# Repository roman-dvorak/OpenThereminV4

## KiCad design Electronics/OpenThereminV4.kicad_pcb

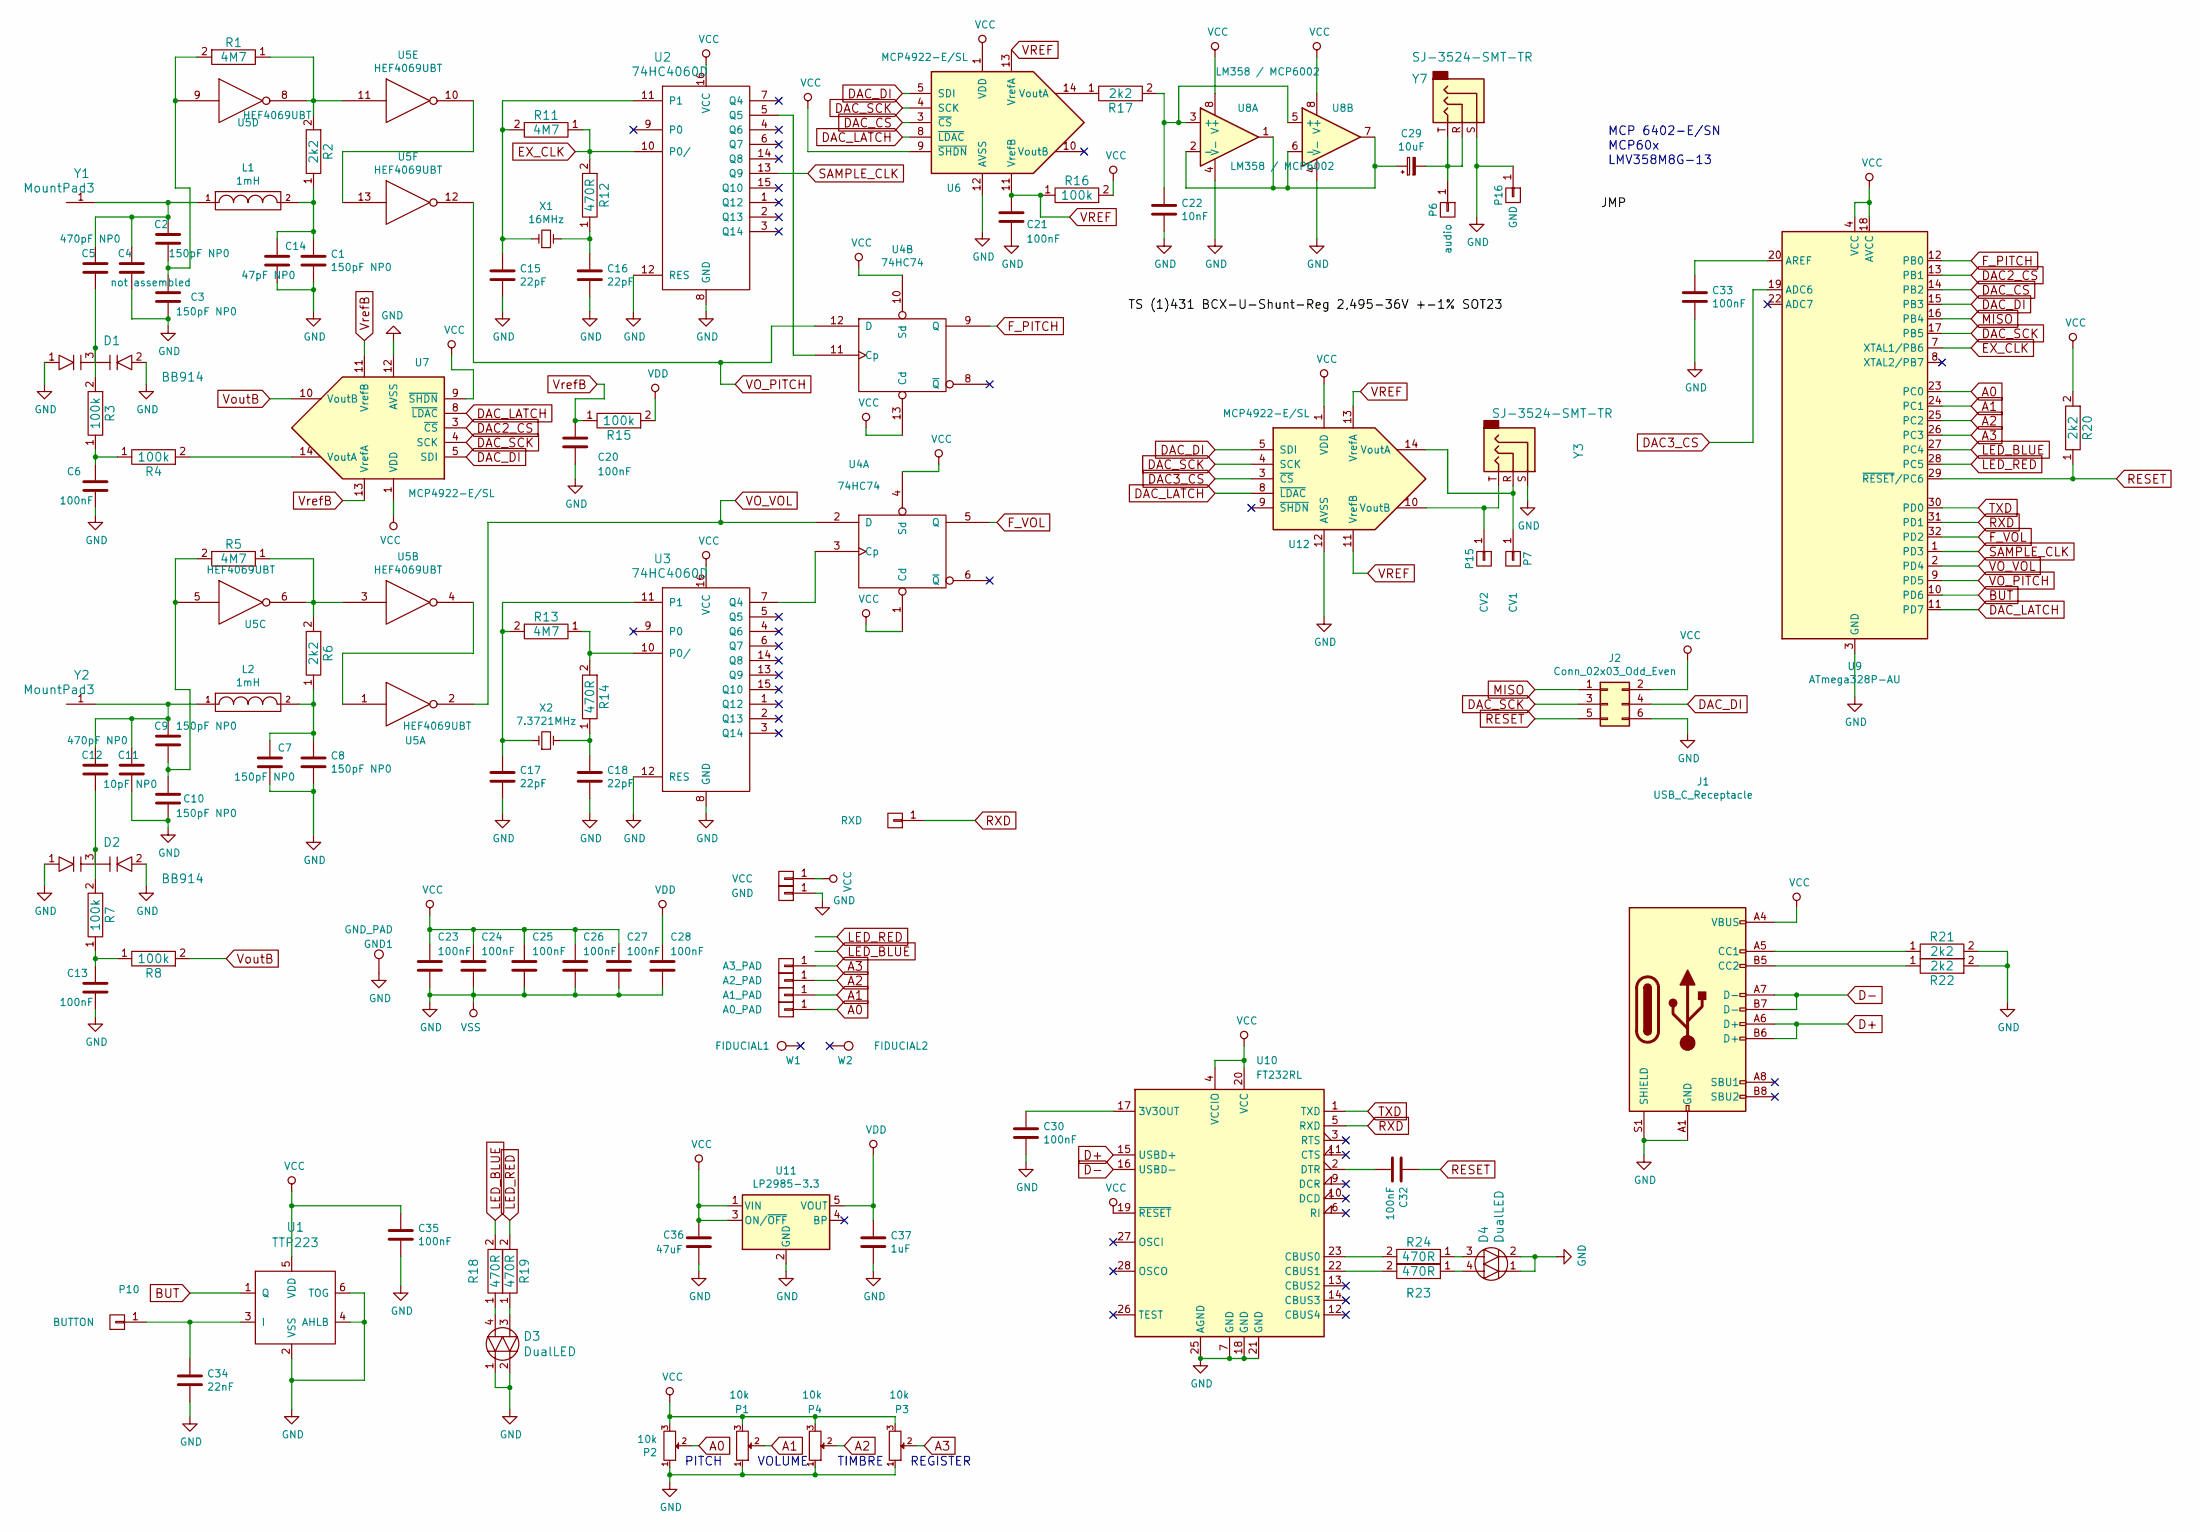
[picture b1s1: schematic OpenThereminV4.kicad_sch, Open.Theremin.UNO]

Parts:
C1, C2, C3, C7, C8, C9, C10: 150pF NP0; C_0603_1608Metric; mouser OK NPO
C4: not assembled; C_0603_1608Metric
C5, C12: 470pF NP0; C_0603_1608Metric; mouser OK NPO
C6, C13, C20, C21, C23, C24, C25, C26, C27, C28, C30, C32, C33, C35: 100nF; C_0603_1608Metric; mouser OK
C11: 10pF NP0; C_0603_1608Metric; mouser OK NPO
C14: 47pF NP0; C_0603_1608Metric; mouser OK NPO
C15, C16, C17, C18: 22pF; C_0603_1608Metric; mouser OK
C22: 10nF; C_0603_1608Metric; mouser OK
C29: 10uF; C_0805_2012Metric; mouser OK
C34: 22nF; C_0603_1608Metric; mouser OK
C36: 47uF; C_1206_3216Metric; mouser OK
C37: 1uF; C_0603_1608Metric; mouser OK
D1, D2: BB914; SOT-23; mouser OK
D3, D4: DualLED; LED_DUAL_WL-SBRW; mouser OK
GND1: GND_PAD; MountingHole_3mm_Pad_Via
J1: USB_C_Receptacle; USBC GCT_USB4105-GF-A; mouser OK
J2: Conn_02x03_Odd_Even; Tag-Connect_TC2030-IDC-NL_2x03_P1.27mm_Vertical
L1, L2: 1mH; L_1812_4532Metric; mouser OK
P1, P2, P3, P4: 10k; PS15NV60; mouser OK
P5: RXD; TestPoint_Pad_1.5x1.5mm
P6: audio; TestPoint_Pad_1.5x1.5mm
P7: CV1; TestPoint_Pad_1.5x1.5mm
P8: VCC; TestPoint_Pad_1.5x1.5mm
P9, P16: GND; TestPoint_Pad_1.5x1.5mm
P10: BUTTON; SensorButton
P11: A3_PAD; TestPoint_Pad_1.5x1.5mm
P12: A2_PAD; TestPoint_Pad_1.5x1.5mm
P13: A1_PAD; TestPoint_Pad_1.5x1.5mm
P14: A0_PAD; TestPoint_Pad_1.5x1.5mm
P15: CV2; TestPoint_Pad_1.5x1.5mm
R1, R5, R11, R13: 4M7; R_0603_1608Metric; mouser OK
R2, R6, R17, R20, R21, R22: 2k2; R_0603_1608Metric; mouser OK
R3, R4, R7, R8, R15, R16: 100k; R_0603_1608Metric; mouser OK
R12, R14, R18, R19, R23, R24: 470R; R_0603_1608Metric; mouser OK
U1: TTP223; SOT-23-6; mouser dratek/dis
U2, U3: 74HC4060D; SOIC-16_3.9x9.9mm_P1.27mm; mouser OK
U4: 74HC74; SOIC-14_3.9x8.7mm_P1.27mm; mouser OK
U5: HEF4069UBT; SOIC-14_3.9x8.7mm_P1.27mm; mouser OK
U6, U7, U12: MCP4922-E/SL; SOIC-14_3.9x8.7mm_P1.27mm; mouser LCSC
U8: LM358 / MCP6002; SOIC-8_3.9x4.9mm_P1.27mm; mouser OK
U9: ATmega328P-AU; TQFP-32_7x7mm_P0.8mm; mouser LCSC
U10: FT232RL; SSOP-28_5.3x10.2mm_P0.65mm; mouser LCSC
U11: LP2985-3.3; SOT-23-5; mouser OK
W1: FIDUCIAL1; Fiducial_1mm_Mask2mm
W2: FIDUCIAL2; Fiducial_1mm_Mask2mm
X1: 16MHz; Crystal_SMD_HC49-SD; mouser OK
X2: 7.3721MHz; Crystal_SMD_HC49-SD; mouser Ok
Y1, Y2: MountPad3; AntennaMountHole; mouser OK
Y3, Y7: SJ-3524-SMT-TR; Jack_3.5mm_CUI_SJ-3524-SMT_Horizontal; mouser OK

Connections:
A0: P2.2, P14.1, U9.23 (PC0)
A1: P1.2, P13.1, U9.24 (PC1)
A2: P4.2, P12.1, U9.25 (PC2)
A3: P3.2, P11.1, U9.26 (PC3)
BUT: U1.1 (Q), U9.10 (PD6)
D+: J1.A6 (D+), J1.B6 (D+), U10.15 (USBD+)
D-: J1.A7 (D-), J1.B7 (D-), U10.16 (USBD-)
DAC2_CS: U7.3 (~CS), U9.13 (PB1)
DAC3_CS: U9.19 (ADC6), U12.3 (~CS)
DAC_CS: U6.3 (~CS), U9.14 (PB2)
DAC_DI: J2.4, U6.5 (SDI), U7.5 (SDI), U9.15 (PB3), U12.5 (SDI)
DAC_LATCH: U6.8 (~LDAC), U7.8 (~LDAC), U9.11 (PD7), U12.8 (~LDAC)
DAC_SCK: J2.3, U6.4 (SCK), U7.4 (SCK), U9.17 (PB5), U12.4 (SCK)
EX_CLK: R11.1, R12.2, U2.10 (P0/), U9.7 (XTAL1/PB6)
F_PITCH: U4.9 (Q), U9.12 (PB0)
F_VOL: U4.5 (Q), U9.32 (PD2)
GND: C1.2, C3.2, C4.2, C6.2, C7.2, C8.2, C10.2, C11.2, C13.2, C14.2, C15.2, C16.2, C17.2, C18.2, C20.2, C21.2, C22.2, C23.2, C24.2, C25.2, C26.2, C27.2, C28.2, C30.2, C33.2, C34.2, C35.2, C36.2, C37.2, D1.1, D1.2, D2.1, D2.2, D3.1, D3.2, D4.1, D4.2, GND1.1, J1.A1 (GND), J1.A12 (GND), J1.B1 (GND), J1.B12 (GND), J1.S1 (SHIELD), J2.6, P1.1, P2.1, P3.1, P4.1, P9.1, P16.1, R21.2, R22.2, U1.2 (VSS), U1.4 (AHLB), U1.6 (TOG), U2.8 (GND), U2.12 (RES), U3.8 (GND), U3.12 (RES), U4.7 (GND), U5.7 (VSS), U6.12 (AVSS), U7.12 (AVSS), U8.4 (V-), U9.3 (GND), U9.5 (GND), U9.21 (GND), U10.7 (GND), U10.18 (GND), U10.21 (GND), U10.25 (AGND), U11.2 (GND), U12.12 (AVSS), Y3.S, Y7.S
LED_BLUE: R18.2, U9.27 (PC4)
LED_RED: R19.2, U9.28 (PC5)
MISO: J2.1, U9.16 (PB4)
unnamed: C1.1, C14.1, L1.2, R2.1
unnamed: C2.1, C4.1, C5.1, L1.1, Y1.1
unnamed: C2.2, C3.1, R1.2, U5.9
unnamed: C5.2, D1.3, R3.2
unnamed: C6.1, R3.1, R4.1
unnamed: C7.1, C8.1, L2.2, R6.1
unnamed: C9.2, C10.1, R5.2, U5.5
unnamed: C9.1, C11.1, C12.1, L2.1, Y2.1
unnamed: C12.2, D2.3, R7.2
unnamed: C13.1, R7.1, R8.1
unnamed: C15.1, R11.2, U2.11 (P1), X1.1
unnamed: C16.1, R12.1, X1.2
unnamed: C17.1, R13.2, U3.11 (P1), X2.1
unnamed: C18.1, R14.1, X2.2
unnamed: C22.1, R17.2, U8.3 (+), U8.5 (+)
unnamed: C29.1, U8.1, U8.2 (-), U8.6 (-), U8.7
unnamed: C29.2, P6.1, Y7.R, Y7.T
unnamed: C30.1, U10.17 (3V3OUT)
unnamed: C32.2, U10.2 (DTR)
unnamed: C33.1, U9.20 (AREF)
unnamed: C34.1, P10.1, U1.3 (I)
unnamed: D3.3, R19.1
unnamed: D3.4, R18.1
unnamed: D4.3, R24.1
unnamed: D4.4, R23.1
unnamed: J1.A5 (CC1), R21.1
unnamed: J1.B5 (CC2), R22.1
unnamed: P7.1, U12.14 (VoutA), Y3.R
unnamed: P15.1, U12.10 (VoutB), Y3.T
unnamed: R1.1, R2.2, U5.8, U5.11
unnamed: R4.2, U7.14 (VoutA)
unnamed: R5.1, R6.2, U5.3, U5.6
unnamed: R13.1, R14.2, U3.10 (P0/)
unnamed: R17.1, U6.14 (VoutA)
unnamed: R23.2, U10.22 (CBUS1)
unnamed: R24.2, U10.23 (CBUS0)
unnamed: U2.5 (Q5), U4.11 (Cp)
unnamed: U3.7 (Q4), U4.3 (Cp)
unnamed: U5.1, U5.4
unnamed: U5.10, U5.13
RESET: C32.1, J2.5, R20.1, U9.29 (~RESET/PC6)
RXD: P5.1, U9.31 (PD1), U10.5 (RXD)
SAMPLE_CLK: U2.13 (Q9), U9.1 (PD3)
TXD: U9.30 (PD0), U10.1 (TXD)
VCC: C23.1, C24.1, C25.1, C26.1, C27.1, C35.1, C36.1, J1.A4 (VBUS), J1.A9 (VBUS), J1.B4 (VBUS), J1.B9 (VBUS), J2.2, P1.3, P2.3, P3.3, P4.3, P8.1, R16.2, R20.2, U1.5 (VDD), U2.16 (VCC), U3.16 (VCC), U4.1 (Cd), U4.4 (Sd), U4.10 (Sd), U4.13 (Cd), U4.14 (VCC), U6.1 (VDD), U6.9 (~SHDN), U7.1 (VDD), U7.9 (~SHDN), U8.8 (V+), U9.4 (VCC), U9.6 (VCC), U9.18 (AVCC), U10.4 (VCCIO), U10.19 (~RESET), U10.20 (VCC), U11.1 (VIN), U11.3 (ON/~OFF), U12.1 (VDD)
VDD: C28.1, C37.1, R15.2, U5.14 (VDD), U11.5 (VOUT)
VO_PITCH: U4.12 (D), U5.12, U9.9 (PD5)
VO_VOL: U4.2 (D), U5.2, U9.2 (PD4)
VREF: C21.1, R16.1, U6.11 (VrefB), U6.13 (VrefA), U12.11 (VrefB), U12.13 (VrefA)
VoutB: R8.2, U7.10 (VoutB)
VrefB: C20.1, R15.1, U7.11 (VrefB), U7.13 (VrefA)

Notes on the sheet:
LMV358M8G-13
REGISTER
TIMBRE
MCP 6402-E/SN
VOLUME
PITCH
MCP60x

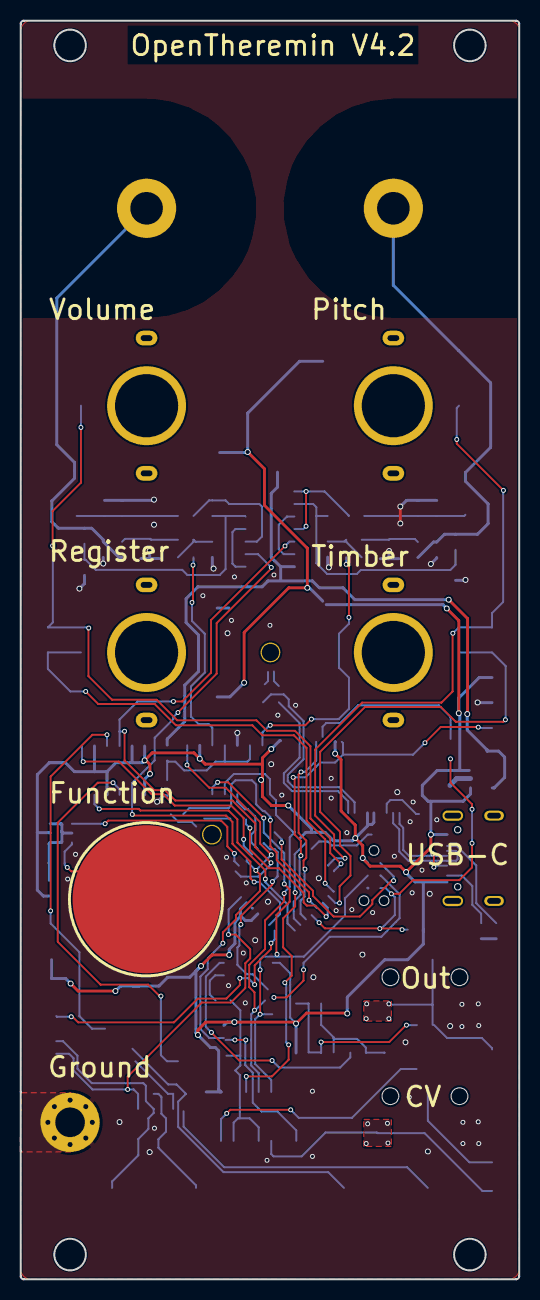
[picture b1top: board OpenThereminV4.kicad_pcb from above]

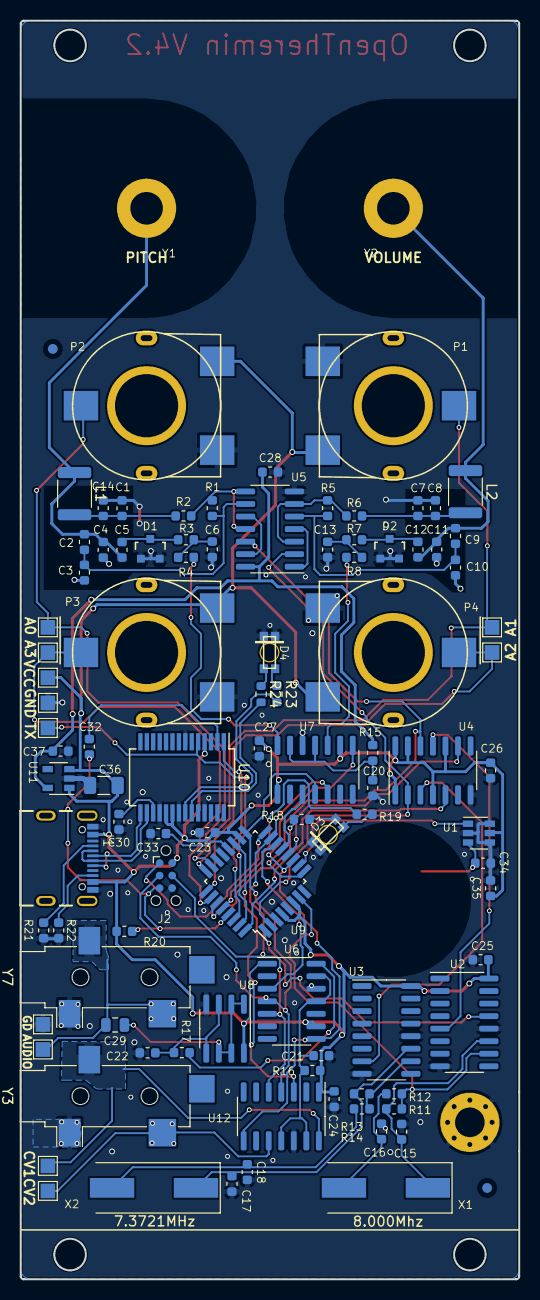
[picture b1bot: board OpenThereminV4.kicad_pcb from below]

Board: 2 copper layers, 50.5 x 127.5 mm, 102 parts (98 on the bottom side), 71 nets.

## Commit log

2022-11-16 clean kicad files, update to kicad v6
2022-11-17 clean design, updates
2022-11-17 add kicad build
2022-11-17 update version of kibot
2022-11-17 update paths
2022-11-17 kibot update
2022-11-17 clean repo
2022-11-17 label update
2022-11-17 Push actions product
2022-11-22 update kicad files
2022-11-25 schematics update
2023-02-22 update files
2023-02-22 update bom
